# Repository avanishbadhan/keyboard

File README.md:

This project is a modular wired keyboard, consisting of a 75% keyboard with an attachable macropad. 
I made this project as a way to learn a variety of things including Schematic and PCB design, as it was my first time working with these; and also to practice some CAD. I have always wanted to know how keyboards work in general, as I use them every single day, and thought this might be a great way to learn, given the opportunity from Hack Club's Blueprint to bring my ideas to life.
Here are some images of CAD and PCB Design, BOM at the end.

|Item                                |Description           |Quantity|Unit Price ($)|Total Price ($)|URL                                                                                                                                                                                                                                                                                                                                                                                                                                                                                                                                                                                                 |Running Total ($ with Tax)|
|------------------------------------|----------------------|--------|--------------|---------------|----------------------------------------------------------------------------------------------------------------------------------------------------------------------------------------------------------------------------------------------------------------------------------------------------------------------------------------------------------------------------------------------------------------------------------------------------------------------------------------------------------------------------------------------------------------------------------------------------|--------------------------|
|SOD-123 Switch Diodes               |Switch Diodes (100pcs)|1       |1.28          |1.28           |https://www.aliexpress.us/item/3256807350544438.html?spm=a2g0o.cart.0.0.2b0e38daTs1TGC&mp=1&pdp_npi=5%40dis%21USD%21USD%201.28%21USD%201.28%21%21USD%201.28%21%21%21%402101e2b017645485039166943ee3e8%2112000041198924897%21ct%21US%216726408924%21%211%210&_gl=1*1g6a37v*_gcl_aw*R0NMLjE3NjMwOTQ5NzEuQ2p3S0NBaUFsTUhJQmhBY0Vpd0FaaFpCVWlaUGEyWEcyT2prSGFWQXNUZFE4cU1KN0xGNktCOWdwNnZhUTZIeDh4cUJnNE5BTTBSVThSb0NSWUlRQXZEX0J3RQ..*_gcl_au*MTUzNzc5ODk1NS4xNzYyNzI0MDg5*_ga*MTgxMzQ1NDY2NC4xNzYyODQwMDIx*_ga_VED1YSGNC7*czE3NjQ1NDgxODQkbzQkZzEkdDE3NjQ1NDg2MjkkajUxJGwwJGgw&gatewayAdapt=glo2usa   |1.28                      |
|Holy Panda Tactile Switches         |MX Switches (110pcs)  |1       |33.3          |33.3           |https://www.aliexpress.us/item/3256805924985540.html?spm=a2g0o.cart.0.0.2b0e38daTs1TGC&mp=1&pdp_npi=5%40dis%21USD%21USD%2033.30%21USD%2014.98%21%21USD%2014.98%21%21%21%402101e2b017645485039166943ee3e8%2112000035800554879%21ct%21US%216726408924%21%211%210&_gl=1*13ht08t*_gcl_aw*R0NMLjE3NjMwOTQ5NzEuQ2p3S0NBaUFsTUhJQmhBY0Vpd0FaaFpCVWlaUGEyWEcyT2prSGFWQXNUZFE4cU1KN0xGNktCOWdwNnZhUTZIeDh4cUJnNE5BTTBSVThSb0NSWUlRQXZEX0J3RQ..*_gcl_au*MTUzNzc5ODk1NS4xNzYyNzI0MDg5*_ga*MTgxMzQ1NDY2NC4xNzYyODQwMDIx*_ga_VED1YSGNC7*czE3NjQ1NDgxODQkbzQkZzEkdDE3NjQ1NDg2MjQkajU2JGwwJGgw&gatewayAdapt=glo2usa|34.58                     |
|PJ-320D Headphone Jack              |TRRS Jack (5pcs)      |1       |1.04          |1.04           |https://www.aliexpress.us/item/3256808202284065.html?spm=a2g0o.cart.0.0.2b0e38daTs1TGC&mp=1&pdp_npi=5%40dis%21USD%21USD%201.04%21USD%201.01%21%21USD%201.01%21%21%21%402101e2b017645485039166943ee3e8%2112000044818551148%21ct%21US%216726408924%21%211%210&_gl=1*1g6a37v*_gcl_aw*R0NMLjE3NjMwOTQ5NzEuQ2p3S0NBaUFsTUhJQmhBY0Vpd0FaaFpCVWlaUGEyWEcyT2prSGFWQXNUZFE4cU1KN0xGNktCOWdwNnZhUTZIeDh4cUJnNE5BTTBSVThSb0NSWUlRQXZEX0J3RQ..*_gcl_au*MTUzNzc5ODk1NS4xNzYyNzI0MDg5*_ga*MTgxMzQ1NDY2NC4xNzYyODQwMDIx*_ga_VED1YSGNC7*czE3NjQ1NDgxODQkbzQkZzEkdDE3NjQ1NDg2MjkkajUxJGwwJGgw&gatewayAdapt=glo2usa   |35.62                     |
|Aux Stereo Cable                    |TRRS Cable            |1       |3.58          |3.58           |https://www.aliexpress.us/item/3256805456527650.html?spm=a2g0o.cart.0.0.60ff38da0HNHgX&mp=1&pdp_npi=5%40dis%21USD%21USD%203.58%21USD%203.58%21%21USD%203.58%21%21%21%402101e2b017645488027332624ee3e8%2112000033857690711%21ct%21US%216726408924%21%211%210&_gl=1*1qixh5w*_gcl_aw*R0NMLjE3NjMwOTQ5NzEuQ2p3S0NBaUFsTUhJQmhBY0Vpd0FaaFpCVWlaUGEyWEcyT2prSGFWQXNUZFE4cU1KN0xGNktCOWdwNnZhUTZIeDh4cUJnNE5BTTBSVThSb0NSWUlRQXZEX0J3RQ..*_gcl_au*MTUzNzc5ODk1NS4xNzYyNzI0MDg5*_ga*MTgxMzQ1NDY2NC4xNzYyODQwMDIx*_ga_VED1YSGNC7*czE3NjQ1NDgxODQkbzQkZzEkdDE3NjQ1NDg4MDMkajEwJGwwJGgw&gatewayAdapt=glo2usa   |39.2                      |
|Nice!Nano V2 Compatible Devboard    |Devboard              |1       |2.89          |2.89           |https://www.aliexpress.us/item/3256809330366531.html?spm=a2g0o.cart.0.0.2b0e38daTs1TGC&mp=1&pdp_npi=5%40dis%21USD%21USD%202.89%21USD%202.89%21%21USD%202.89%21%21%21%402101e2b017645485039166943ee3e8%2112000049341617471%21ct%21US%216726408924%21%211%210&_gl=1*13ht08t*_gcl_aw*R0NMLjE3NjMwOTQ5NzEuQ2p3S0NBaUFsTUhJQmhBY0Vpd0FaaFpCVWlaUGEyWEcyT2prSGFWQXNUZFE4cU1KN0xGNktCOWdwNnZhUTZIeDh4cUJnNE5BTTBSVThSb0NSWUlRQXZEX0J3RQ..*_gcl_au*MTUzNzc5ODk1NS4xNzYyNzI0MDg5*_ga*MTgxMzQ1NDY2NC4xNzYyODQwMDIx*_ga_VED1YSGNC7*czE3NjQ1NDgxODQkbzQkZzEkdDE3NjQ1NDg2MjQkajU2JGwwJGgw&gatewayAdapt=glo2usa   |42.09                     |
|Arduino ProMicro Compatible Devboard|Devboard              |1       |6.23          |6.23           |https://www.aliexpress.us/item/3256805885300100.html?spm=a2g0o.cart.0.0.2b0e38daTs1TGC&mp=1&pdp_npi=5%40dis%21USD%21USD%206.23%21USD%206.23%21%21USD%206.23%21%21%21%402101e2b017645485039166943ee3e8%2112000035596486720%21ct%21US%216726408924%21%211%210&_gl=1*13ht08t*_gcl_aw*R0NMLjE3NjMwOTQ5NzEuQ2p3S0NBaUFsTUhJQmhBY0Vpd0FaaFpCVWlaUGEyWEcyT2prSGFWQXNUZFE4cU1KN0xGNktCOWdwNnZhUTZIeDh4cUJnNE5BTTBSVThSb0NSWUlRQXZEX0J3RQ..*_gcl_au*MTUzNzc5ODk1NS4xNzYyNzI0MDg5*_ga*MTgxMzQ1NDY2NC4xNzYyODQwMDIx*_ga_VED1YSGNC7*czE3NjQ1NDgxODQkbzQkZzEkdDE3NjQ1NDg2MjQkajU2JGwwJGgw&gatewayAdapt=glo2usa   |48.32                     |
|Keycaps                             |MX Keycaps (123pcs)   |1       |11.33         |11.33          |https://www.aliexpress.us/item/3256808975886837.html?spm=a2g0o.cart.0.0.2b0e38daTs1TGC&mp=1&pdp_npi=5%40dis%21USD%21USD%2011.33%21USD%2010.14%21%21USD%2010.14%21%21%21%402101e2b017645485039166943ee3e8%2112000050747623051%21ct%21US%216726408924%21%211%210&_gl=1*1hfs13x*_gcl_aw*R0NMLjE3NjMwOTQ5NzEuQ2p3S0NBaUFsTUhJQmhBY0Vpd0FaaFpCVWlaUGEyWEcyT2prSGFWQXNUZFE4cU1KN0xGNktCOWdwNnZhUTZIeDh4cUJnNE5BTTBSVThSb0NSWUlRQXZEX0J3RQ..*_gcl_au*MTUzNzc5ODk1NS4xNzYyNzI0MDg5*_ga*MTgxMzQ1NDY2NC4xNzYyODQwMDIx*_ga_VED1YSGNC7*czE3NjQ1NDgxODQkbzQkZzEkdDE3NjQ1NDg0ODYkajUxJGwwJGgw&gatewayAdapt=glo2usa|59.65                     |
|Solder Paste                        |Solder Paste (2pcs)   |1       |8.11          |8.11           |https://www.aliexpress.us/item/3256806722346427.html?spm=a2g0o.cart.0.0.2b0e38daTs1TGC&mp=1&pdp_npi=5%40dis%21USD%21USD%208.11%21USD%203.98%21%21USD%203.98%21%21%21%402101e2b017645485039166943ee3e8%2112000038683881200%21ct%21US%216726408924%21%211%210&_gl=1*1o3vfg6*_gcl_aw*R0NMLjE3NjMwOTQ5NzEuQ2p3S0NBaUFsTUhJQmhBY0Vpd0FaaFpCVWlaUGEyWEcyT2prSGFWQXNUZFE4cU1KN0xGNktCOWdwNnZhUTZIeDh4cUJnNE5BTTBSVThSb0NSWUlRQXZEX0J3RQ..*_gcl_au*MTUzNzc5ODk1NS4xNzYyNzI0MDg5*_ga*MTgxMzQ1NDY2NC4xNzYyODQwMDIx*_ga_VED1YSGNC7*czE3NjQ1NDgxODQkbzQkZzEkdDE3NjQ1NDg2MzEkajQ5JGwwJGgw&gatewayAdapt=glo2usa   |67.76                     |
|Mounted Snap-In MX Stabilizers      |MX Stabilizers        |2       |3.88          |7.76           |https://www.aliexpress.us/item/3256808413621831.html?spm=a2g0o.cart.0.0.4a1a38daFEW9pV&mp=1&pdp_npi=5%40dis%21USD%21USD%203.88%21USD%203.10%21%21USD%203.10%21%21%21%402101dedf17645490190322157e3f6b%2112000045897350110%21ct%21US%216726408924%21%212%210&_gl=1*g0usif*_gcl_aw*R0NMLjE3NjMwOTQ5NzEuQ2p3S0NBaUFsTUhJQmhBY0Vpd0FaaFpCVWlaUGEyWEcyT2prSGFWQXNUZFE4cU1KN0xGNktCOWdwNnZhUTZIeDh4cUJnNE5BTTBSVThSb0NSWUlRQXZEX0J3RQ..*_gcl_au*MTUzNzc5ODk1NS4xNzYyNzI0MDg5*_ga*MTgxMzQ1NDY2NC4xNzYyODQwMDIx*_ga_VED1YSGNC7*czE3NjQ1NDgxODQkbzQkZzEkdDE3NjQ1NDkwMTUkajYwJGwwJGgw&gatewayAdapt=glo2usa    |75.52                     |
|M2 22mm Countersunk Screws          |Screws (20pcs)        |1       |2.02          |2.02           |https://www.aliexpress.us/item/3256808624582928.html?spm=a2g0o.cart.0.0.2b0e38daTs1TGC&mp=1&pdp_npi=5%40dis%21USD%21USD%202.02%21USD%200.99%21%21USD%200.99%21%21%21%402101e2b017645485039166943ee3e8%2112000046763245370%21ct%21US%216726408924%21%211%210&_gl=1*sjgpuf*_gcl_aw*R0NMLjE3NjMwOTQ5NzEuQ2p3S0NBaUFsTUhJQmhBY0Vpd0FaaFpCVWlaUGEyWEcyT2prSGFWQXNUZFE4cU1KN0xGNktCOWdwNnZhUTZIeDh4cUJnNE5BTTBSVThSb0NSWUlRQXZEX0J3RQ..*_gcl_au*MTUzNzc5ODk1NS4xNzYyNzI0MDg5*_ga*MTgxMzQ1NDY2NC4xNzYyODQwMDIx*_ga_VED1YSGNC7*czE3NjQ1NDgxODQkbzQkZzEkdDE3NjQ1NDg2MjAkajYwJGwwJGgw&gatewayAdapt=glo2usa    |77.54                     |
|Keyboard Gasket Foam Strip          |Gasket Foam (20pcs)   |1       |4.59          |4.59           |https://www.aliexpress.us/item/3256804614353215.html?spm=a2g0o.cart.0.0.2b0e38daTs1TGC&mp=1&pdp_npi=5%40dis%21USD%21USD%204.59%21USD%204.59%21%21USD%204.59%21%21%21%402101e2b017645485039166943ee3e8%2112000030535225384%21ct%21US%216726408924%21%211%210&_gl=1*sjgpuf*_gcl_aw*R0NMLjE3NjMwOTQ5NzEuQ2p3S0NBaUFsTUhJQmhBY0Vpd0FaaFpCVWlaUGEyWEcyT2prSGFWQXNUZFE4cU1KN0xGNktCOWdwNnZhUTZIeDh4cUJnNE5BTTBSVThSb0NSWUlRQXZEX0J3RQ..*_gcl_au*MTUzNzc5ODk1NS4xNzYyNzI0MDg5*_ga*MTgxMzQ1NDY2NC4xNzYyODQwMDIx*_ga_VED1YSGNC7*czE3NjQ1NDgxODQkbzQkZzEkdDE3NjQ1NDg2MjAkajYwJGwwJGgw&gatewayAdapt=glo2usa    |82.13                     |

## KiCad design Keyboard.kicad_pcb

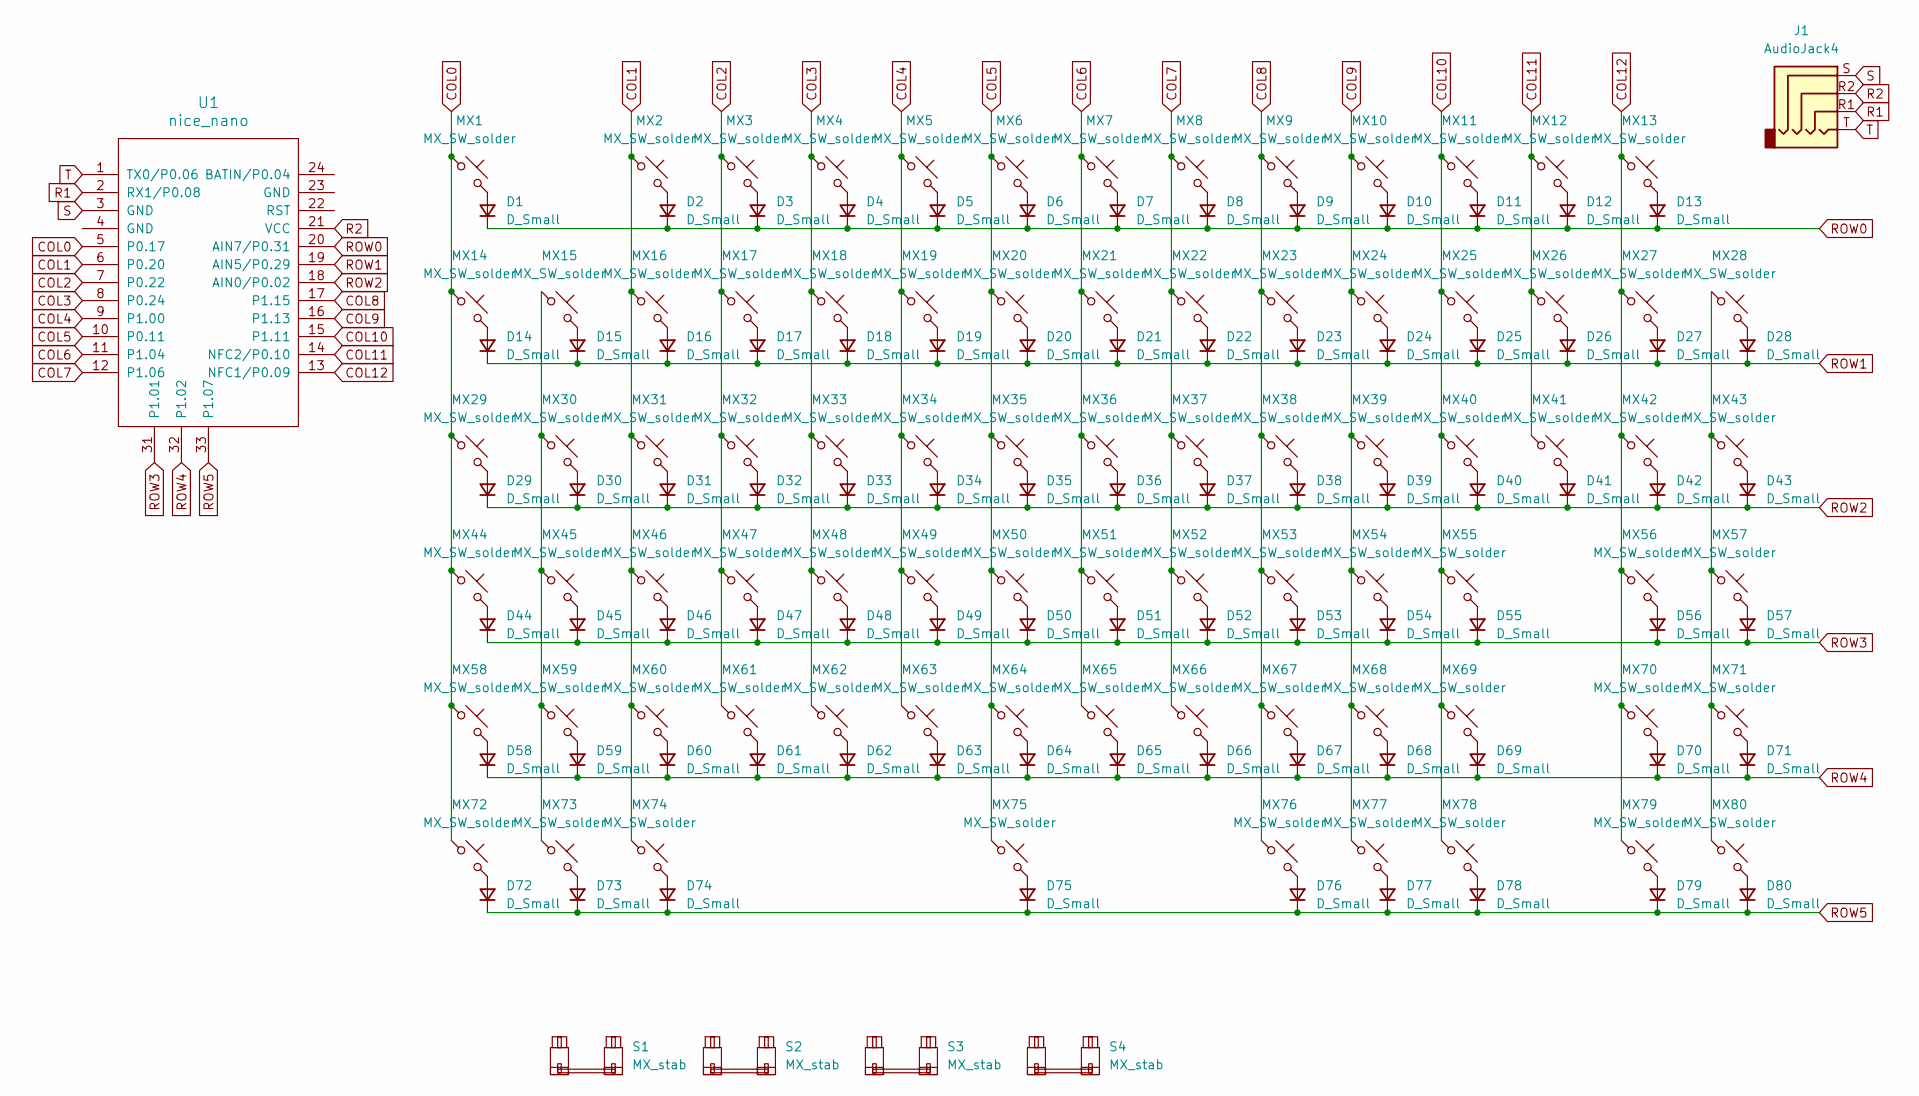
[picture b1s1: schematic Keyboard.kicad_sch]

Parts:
D1, D2, D3, D4, D5, D6, D7, D8, D9, D10, D11, D12, D13, D14, D15, D16, D17, D18, D19, D20, D21, D22, D23, D24, D25, D26, D27, D28, D29, D30, D31, D32, D33, D34, D35, D36, D37, D38, D39, D40, D41, D42, D43, D44, D45, D46, D47, D48, D49, D50, D51, D52, D53, D54, D55, D56, D57, D58, D59, D60, D61, D62, D63, D64, D65, D66, D67, D68, D69, D70, D71, D72, D73, D74, D75, D76, D77, D78, D79, D80: D_Small; D_SOD-123
J1: AudioJack4; Jack_3.5mm_PJ320D_Horizontal
MX1, MX2, MX3, MX4, MX5, MX6, MX7, MX8, MX9, MX10, MX11, MX12, MX13, MX14, MX15, MX16, MX17, MX18, MX19, MX20, MX21, MX22, MX23, MX24, MX25, MX26, MX27, MX28, MX30, MX31, MX32, MX33, MX34, MX35, MX36, MX37, MX38, MX39, MX40, MX41, MX43, MX45, MX46, MX47, MX48, MX49, MX50, MX51, MX52, MX53, MX54, MX55, MX56, MX57, MX58, MX59, MX60, MX61, MX62, MX63, MX64, MX65, MX66, MX67, MX68, MX70, MX71, MX75, MX78, MX79, MX80: MX_SW_solder; SW_MX_1u
MX29, MX42: MX_SW_solder; SW_MX_1.5u
MX44, MX69: MX_SW_solder; SW_MX_1.75u
MX72, MX73, MX74, MX76, MX77: MX_SW_solder; SW_MX_1.25u
S1: MX_stab; STAB_MX_P_2u
S2, S3: MX_stab; STAB_MX_P_2.25u
S4: MX_stab; STAB_MX_P_6.25u
U1: nice_nano; nice_nano_AH_Reversible

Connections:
COL0: MX1.1, MX14.1, MX29.1, MX44.1, MX58.1, MX72.1, U1.5 (P0.17)
COL1: MX2.1, MX16.1, MX31.1, MX46.1, MX60.1, MX74.1, U1.6 (P0.20)
COL2: MX3.1, MX17.1, MX32.1, MX47.1, MX61.1, U1.7 (P0.22)
COL3: MX4.1, MX18.1, MX33.1, MX48.1, MX62.1, U1.8 (P0.24)
COL4: MX5.1, MX19.1, MX34.1, MX49.1, MX63.1, U1.9 (P1.00)
COL5: MX6.1, MX20.1, MX35.1, MX50.1, MX64.1, MX75.1, U1.10 (P0.11)
COL6: MX7.1, MX21.1, MX36.1, MX51.1, MX65.1, U1.11 (P1.04)
COL7: MX8.1, MX22.1, MX37.1, MX52.1, MX66.1, U1.12 (P1.06)
COL8: MX9.1, MX23.1, MX38.1, MX53.1, MX67.1, MX76.1, U1.17 (P1.15)
COL9: MX10.1, MX24.1, MX39.1, MX54.1, MX68.1, MX77.1, U1.16 (P1.13)
COL10: MX11.1, MX25.1, MX40.1, MX55.1, MX69.1, MX78.1, U1.15 (P1.11)
COL11: MX12.1, MX26.1, MX41.1, U1.14 (NFC2/P0.10)
COL12: MX13.1, MX27.1, MX42.1, MX56.1, MX70.1, MX79.1, U1.13 (NFC1/P0.09)
unnamed: D1.2 (A), MX1.2
unnamed: D2.2 (A), MX2.2
unnamed: D3.2 (A), MX3.2
unnamed: D4.2 (A), MX4.2
unnamed: D5.2 (A), MX5.2
unnamed: D6.2 (A), MX6.2
unnamed: D7.2 (A), MX7.2
unnamed: D8.2 (A), MX8.2
unnamed: D9.2 (A), MX9.2
unnamed: D10.2 (A), MX10.2
unnamed: D11.2 (A), MX11.2
unnamed: D12.2 (A), MX12.2
unnamed: D13.2 (A), MX13.2
unnamed: D14.2 (A), MX14.2
unnamed: D15.2 (A), MX15.2
unnamed: D16.2 (A), MX16.2
unnamed: D17.2 (A), MX17.2
unnamed: D18.2 (A), MX18.2
unnamed: D19.2 (A), MX19.2
unnamed: D20.2 (A), MX20.2
unnamed: D21.2 (A), MX21.2
unnamed: D22.2 (A), MX22.2
unnamed: D23.2 (A), MX23.2
unnamed: D24.2 (A), MX24.2
unnamed: D25.2 (A), MX25.2
unnamed: D26.2 (A), MX26.2
unnamed: D27.2 (A), MX27.2
unnamed: D28.2 (A), MX28.2
unnamed: D29.2 (A), MX29.2
unnamed: D30.2 (A), MX30.2
unnamed: D31.2 (A), MX31.2
unnamed: D32.2 (A), MX32.2
unnamed: D33.2 (A), MX33.2
unnamed: D34.2 (A), MX34.2
unnamed: D35.2 (A), MX35.2
unnamed: D36.2 (A), MX36.2
unnamed: D37.2 (A), MX37.2
unnamed: D38.2 (A), MX38.2
unnamed: D39.2 (A), MX39.2
unnamed: D40.2 (A), MX40.2
unnamed: D41.2 (A), MX41.2
unnamed: D42.2 (A), MX42.2
unnamed: D43.2 (A), MX43.2
unnamed: D44.2 (A), MX44.2
unnamed: D45.2 (A), MX45.2
unnamed: D46.2 (A), MX46.2
unnamed: D47.2 (A), MX47.2
unnamed: D48.2 (A), MX48.2
unnamed: D49.2 (A), MX49.2
unnamed: D50.2 (A), MX50.2
unnamed: D51.2 (A), MX51.2
unnamed: D52.2 (A), MX52.2
unnamed: D53.2 (A), MX53.2
unnamed: D54.2 (A), MX54.2
unnamed: D55.2 (A), MX55.2
unnamed: D56.2 (A), MX56.2
unnamed: D57.2 (A), MX57.2
unnamed: D58.2 (A), MX58.2
unnamed: D59.2 (A), MX59.2
unnamed: D60.2 (A), MX60.2
unnamed: D61.2 (A), MX61.2
unnamed: D62.2 (A), MX62.2
unnamed: D63.2 (A), MX63.2
unnamed: D64.2 (A), MX64.2
unnamed: D65.2 (A), MX65.2
unnamed: D66.2 (A), MX66.2
unnamed: D67.2 (A), MX67.2
unnamed: D68.2 (A), MX68.2
unnamed: D69.2 (A), MX69.2
unnamed: D70.2 (A), MX70.2
unnamed: D71.2 (A), MX71.2
unnamed: D72.2 (A), MX72.2
unnamed: D73.2 (A), MX73.2
unnamed: D74.2 (A), MX74.2
unnamed: D75.2 (A), MX75.2
unnamed: D76.2 (A), MX76.2
unnamed: D77.2 (A), MX77.2
unnamed: D78.2 (A), MX78.2
unnamed: D79.2 (A), MX79.2
unnamed: D80.2 (A), MX80.2
unnamed: MX15.1, MX30.1, MX45.1, MX59.1, MX73.1
unnamed: MX28.1, MX43.1, MX57.1, MX71.1, MX80.1
R1: J1.R1, U1.2 (RX1/P0.08)
R2: J1.R2, U1.21 (VCC)
ROW0: D1.1 (K), D2.1 (K), D3.1 (K), D4.1 (K), D5.1 (K), D6.1 (K), D7.1 (K), D8.1 (K), D9.1 (K), D10.1 (K), D11.1 (K), D12.1 (K), D13.1 (K), U1.20 (AIN7/P0.31)
ROW1: D14.1 (K), D15.1 (K), D16.1 (K), D17.1 (K), D18.1 (K), D19.1 (K), D20.1 (K), D21.1 (K), D22.1 (K), D23.1 (K), D24.1 (K), D25.1 (K), D26.1 (K), D27.1 (K), D28.1 (K), U1.19 (AIN5/P0.29)
ROW2: D29.1 (K), D30.1 (K), D31.1 (K), D32.1 (K), D33.1 (K), D34.1 (K), D35.1 (K), D36.1 (K), D37.1 (K), D38.1 (K), D39.1 (K), D40.1 (K), D41.1 (K), D42.1 (K), D43.1 (K), U1.18 (AIN0/P0.02)
ROW3: D44.1 (K), D45.1 (K), D46.1 (K), D47.1 (K), D48.1 (K), D49.1 (K), D50.1 (K), D51.1 (K), D52.1 (K), D53.1 (K), D54.1 (K), D55.1 (K), D56.1 (K), D57.1 (K), U1.31 (P1.01)
ROW4: D58.1 (K), D59.1 (K), D60.1 (K), D61.1 (K), D62.1 (K), D63.1 (K), D64.1 (K), D65.1 (K), D66.1 (K), D67.1 (K), D68.1 (K), D69.1 (K), D70.1 (K), D71.1 (K), U1.32 (P1.02)
ROW5: D72.1 (K), D73.1 (K), D74.1 (K), D75.1 (K), D76.1 (K), D77.1 (K), D78.1 (K), D79.1 (K), D80.1 (K), U1.33 (P1.07)
S: J1.S, U1.3 (GND)
T: J1.T, U1.1 (TX0/P0.06)

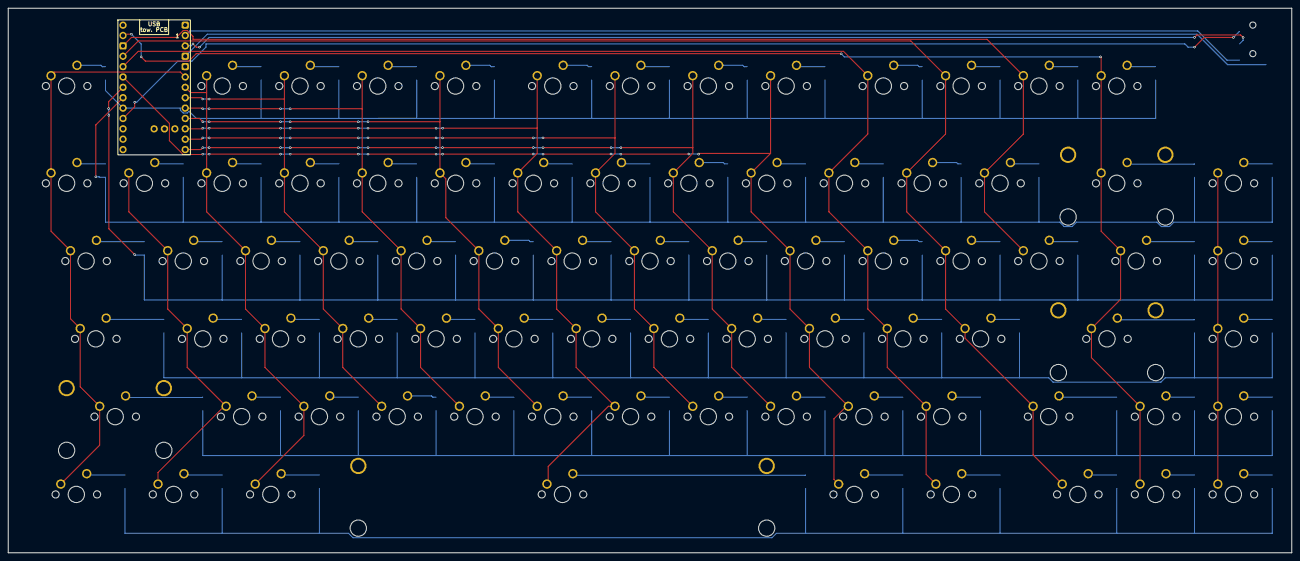
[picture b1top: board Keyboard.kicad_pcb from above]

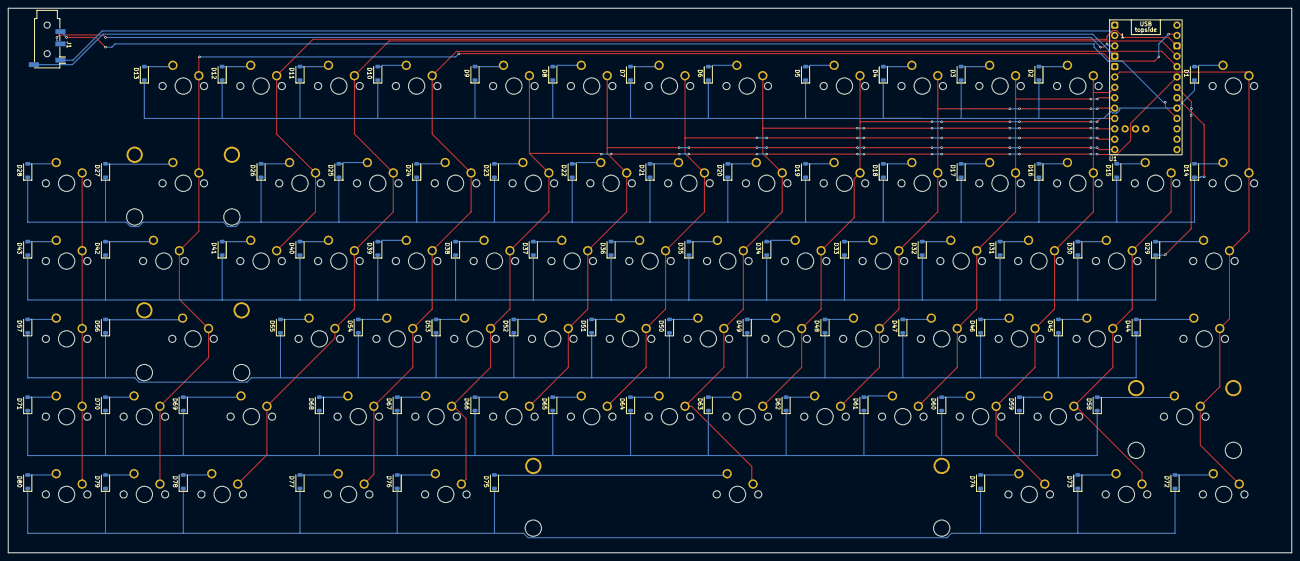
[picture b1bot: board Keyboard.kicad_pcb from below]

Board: 2 copper layers, 314.3 x 133.4 mm, 166 parts (82 on the bottom side), 105 nets.

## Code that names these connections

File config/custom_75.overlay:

/ {
    chosen {
        zmk,kscan = &kscan0;
    };

    kscan0: kscan_composite {
        compatible = "zmk,kscan-gpio-matrix";
        label = "KSCAN";
        diode-direction = "col2row";

        row-gpios
            = <&pro_micro 14 (GPIO_ACTIVE_HIGH | GPIO_PULL_DOWN)> // ROW0
            , <&pro_micro 15 (GPIO_ACTIVE_HIGH | GPIO_PULL_DOWN)> // ROW1
            , <&pro_micro 18 (GPIO_ACTIVE_HIGH | GPIO_PULL_DOWN)> // ROW2
            , <&pro_micro 19 (GPIO_ACTIVE_HIGH | GPIO_PULL_DOWN)> // ROW3
            , <&pro_micro 20 (GPIO_ACTIVE_HIGH | GPIO_PULL_DOWN)> // ROW4
            , <&pro_micro 21 (GPIO_ACTIVE_HIGH | GPIO_PULL_DOWN)> // ROW5
            ;

        col-gpios
            = <&pro_micro 1  GPIO_ACTIVE_HIGH> // COL0
            , <&pro_micro 2  GPIO_ACTIVE_HIGH> // COL1
            , <&pro_micro 3  GPIO_ACTIVE_HIGH> // COL2
            , <&pro_micro 4  GPIO_ACTIVE_HIGH> // COL3
            , <&pro_micro 5  GPIO_ACTIVE_HIGH> // COL4
            , <&pro_micro 6  GPIO_ACTIVE_HIGH> // COL5
            , <&pro_micro 7  GPIO_ACTIVE_HIGH> // COL6
            , <&pro_micro 8  GPIO_ACTIVE_HIGH> // COL7
            , <&pro_micro 9  GPIO_ACTIVE_HIGH> // COL8
            , <&pro_micro 10 GPIO_ACTIVE_HIGH> // COL9
            , <&pro_micro 16 GPIO_ACTIVE_HIGH> // COL10
            , <&pro_micro 14 GPIO_ACTIVE_HIGH> // COL11
            , <&pro_micro 13 GPIO_ACTIVE_HIGH> // COL12
            ;
    };
};

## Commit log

2025-11-08 kicad project files
2025-11-08 project files
2025-11-08 75% keyboard and macropad
2025-11-08 kicad files
2025-11-09 kicad + CAD files
    CAD was created using Autodesk Inventor
2025-12-05 KiCad files to repo
2026-06-12 Create Kconfig
2026-06-12 Update Kconfig
